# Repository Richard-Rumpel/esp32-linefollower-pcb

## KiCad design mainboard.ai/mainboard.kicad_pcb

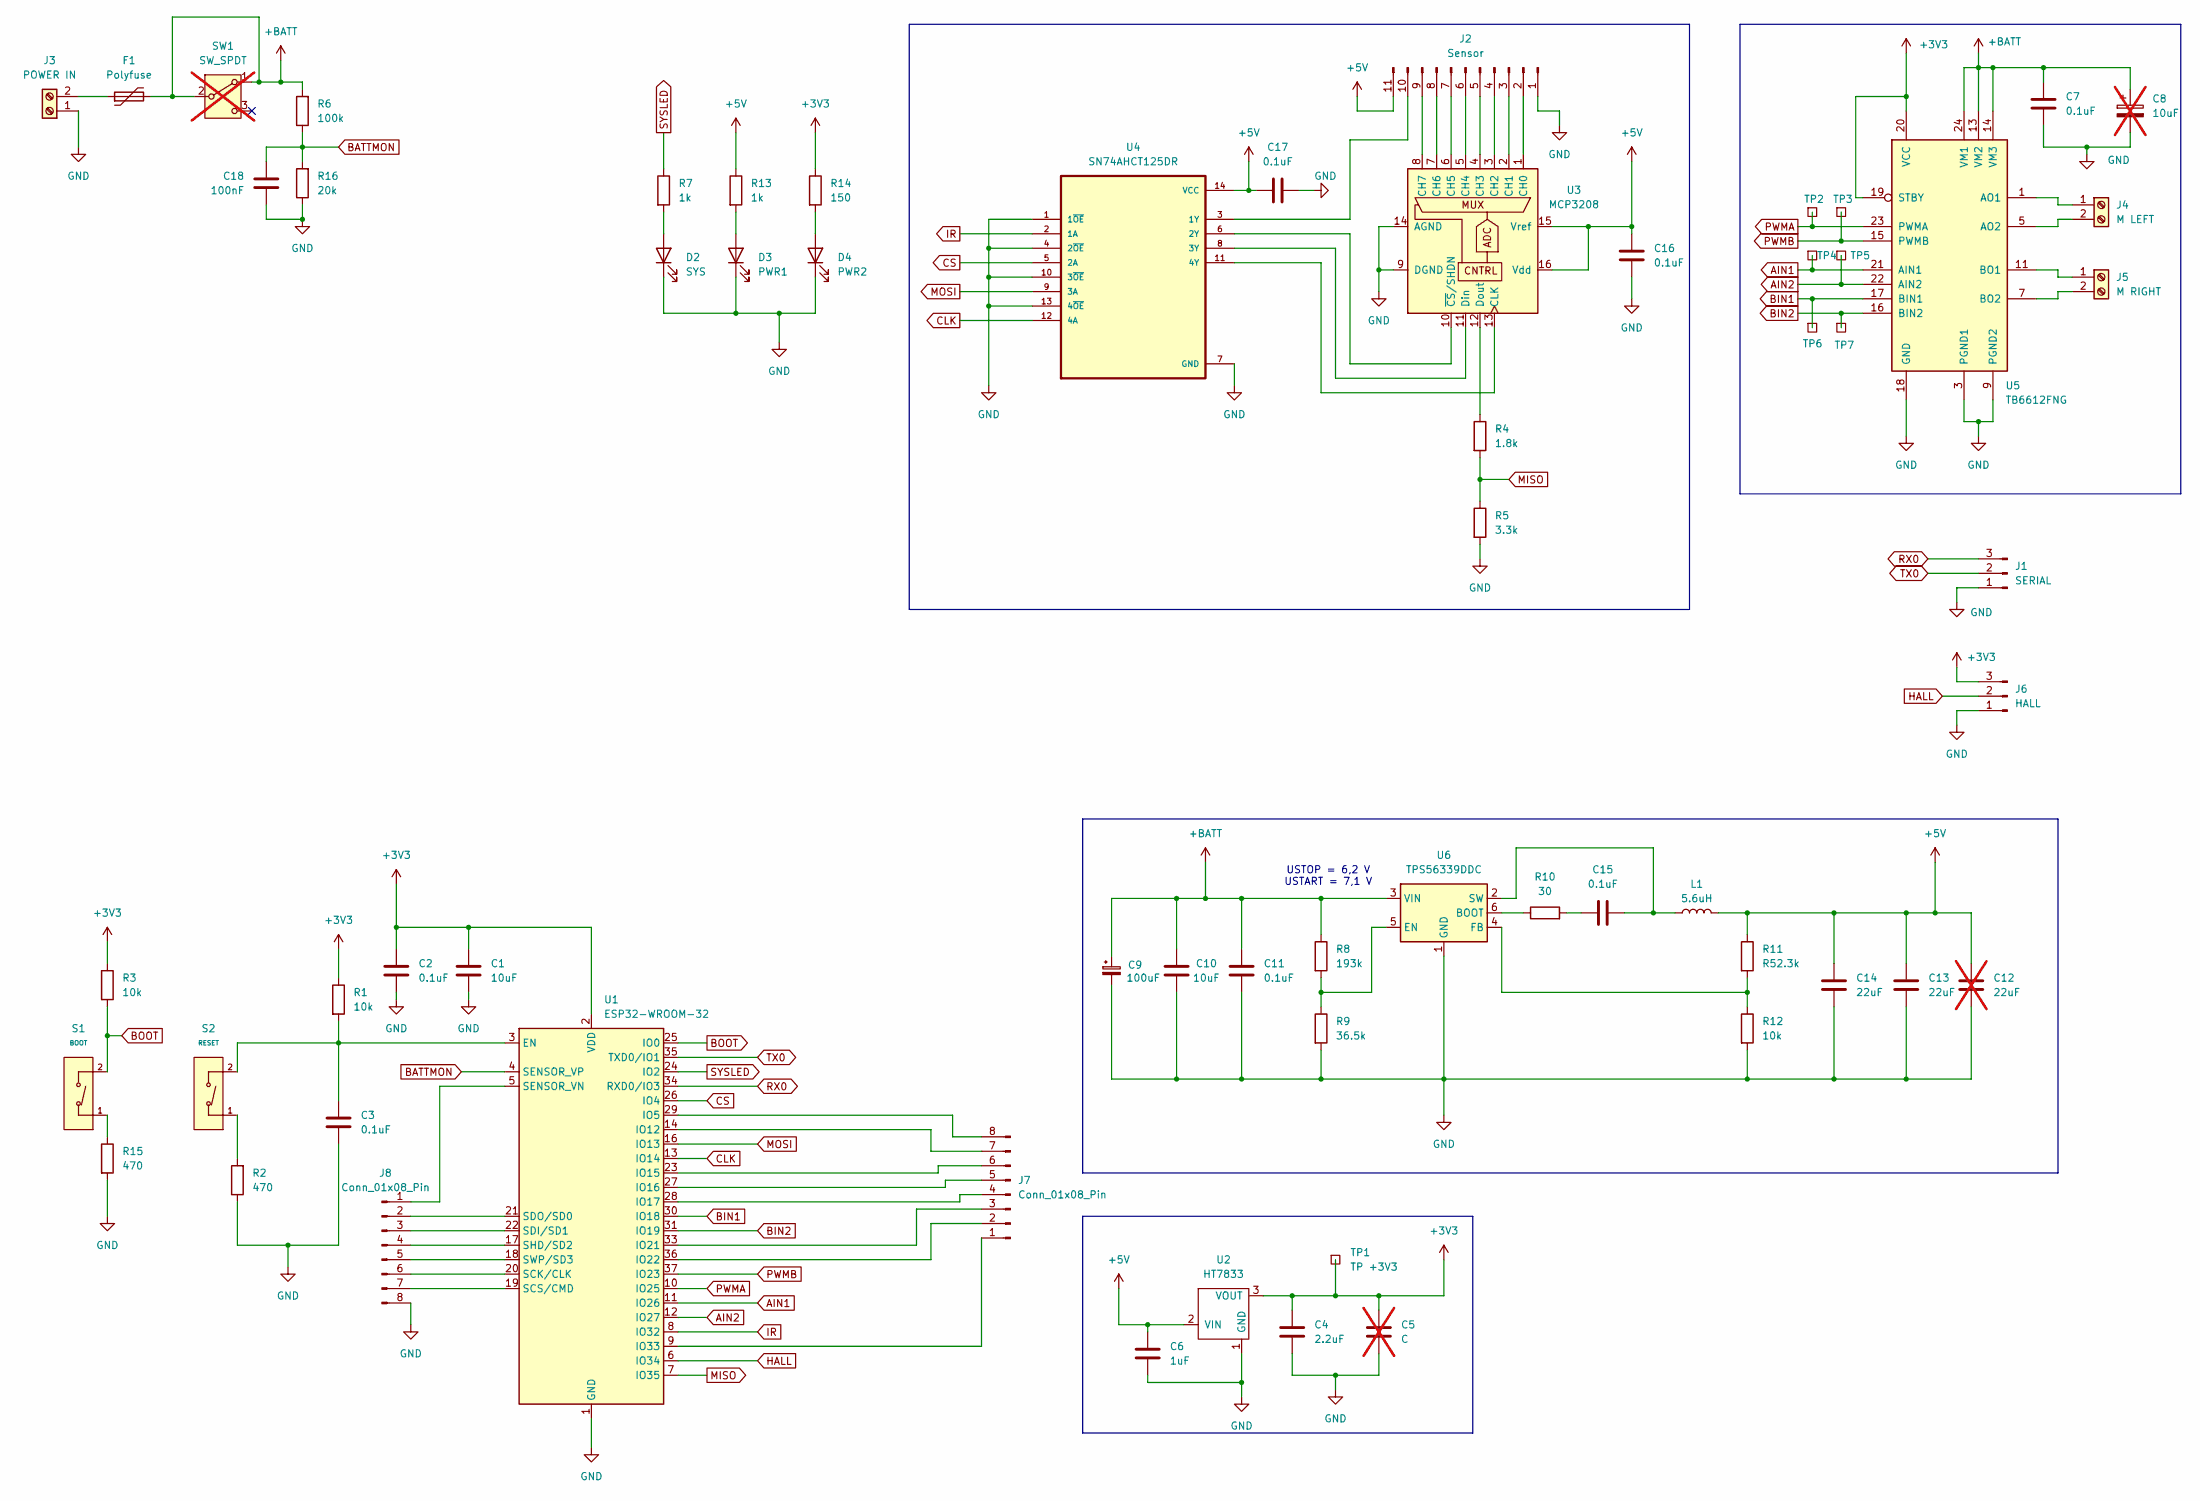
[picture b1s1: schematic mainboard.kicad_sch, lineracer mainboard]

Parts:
C1: 10uF; C_0603_1608Metric_Pad1.08x0.95mm_HandSolder; LCSC C1691
C2, C3: 0.1uF; C_0603_1608Metric_Pad1.08x0.95mm_HandSolder; LCSC C1590
C4: 2.2uF; C_0603_1608Metric_Pad1.08x0.95mm_HandSolder; LCSC C23630
C5: C; not fitted
C6: 1uF; C_0603_1608Metric_Pad1.08x0.95mm_HandSolder; LCSC C14664
C7: 0.1uF; C_0603_1608Metric_Pad1.08x0.95mm_HandSolder; LCSC C15850
C8: 10uF; not fitted
C9: 100uF; CP_Elec_6.3x7.7
C10: 10uF; C_0805_2012Metric_Pad1.18x1.45mm_HandSolder; LCSC C15850
C11, C16, C17: 0.1uF; C_0805_2012Metric_Pad1.18x1.45mm_HandSolder; LCSC C15850
C12: 22uF; not fitted
C13, C14: 22uF; C_0805_2012Metric_Pad1.18x1.45mm_HandSolder; LCSC C98190
C15: 0.1uF; C_0603_1608Metric_Pad1.08x0.95mm_HandSolder; LCSC C1591
C18: 100nF; C_0603_1608Metric_Pad1.08x0.95mm_HandSolder; LCSC C14663
D2: SYS; LED_0603_1608Metric_Pad1.05x0.95mm_HandSolder; LCSC C2286
D3: PWR1; LED_0603_1608Metric_Pad1.05x0.95mm_HandSolder; LCSC C2287
D4: PWR2; LED_0603_1608Metric_Pad1.05x0.95mm_HandSolder; LCSC C2288
F1: Polyfuse; Fuse_1812_4532Metric; LCSC C20812
J1: SERIAL; PinHeader_1x03_P2.54mm_Vertical
J2: Sensor; PinHeader_1x11_P2.54mm_Vertical
J3: POWER IN; TerminalBlock_Kangnex_WJ300V-5.0-2P_1x02_P5.00mm; LCSC C8385
J4: M LEFT; TerminalBlock_Kangnex_WJ300V-5.0-2P_1x02_P5.00mm; LCSC C8385
J5: M RIGHT; TerminalBlock_Kangnex_WJ300V-5.0-2P_1x02_P5.00mm; LCSC C8385
J6: HALL; PinHeader_1x03_P2.54mm_Vertical
J7, J8: Conn_01x08_Pin; PinHeader_1x08_P2.54mm_Vertical
L1: 5.6uH; L_0530CDMCCDS_5.4x5.2mm; LCSC C2961888
R1, R3: 10k; R_0603_1608Metric_Pad0.98x0.95mm_HandSolder; LCSC C25804
R2, R15: 470; R_0603_1608Metric_Pad0.98x0.95mm_HandSolder; LCSC C23179
R4: 1.8k; R_0603_1608Metric_Pad0.98x0.95mm_HandSolder; LCSC C4177
R5: 3.3k; R_0603_1608Metric_Pad0.98x0.95mm_HandSolder; LCSC C22978
R6: 100k; R_0603_1608Metric_Pad0.98x0.95mm_HandSolder; LCSC C25803
R7, R13: 1k; R_0603_1608Metric_Pad0.98x0.95mm_HandSolder; LCSC C21190
R8: 193k; R_0603_1608Metric_Pad0.98x0.95mm_HandSolder; LCSC C22932
R9: 36.5k; R_0603_1608Metric_Pad0.98x0.95mm_HandSolder; LCSC C23029
R10: 30; R_0603_1608Metric_Pad0.98x0.95mm_HandSolder; LCSC C22985
R11: R52.3k; R_0603_1608Metric_Pad0.98x0.95mm_HandSolder; LCSC C23198
R12: 10k; R_0603_1608Metric_Pad0.98x0.95mm_HandSolder; LCSC C98220
R14: 150; R_0603_1608Metric_Pad0.98x0.95mm_HandSolder; LCSC C22808
R16: 20k; R_0603_1608Metric_Pad0.98x0.95mm_HandSolder; LCSC C4184
S1: BOOT; SW_TS-1088-AR02016; Voltage Rating (Dc) 12V; Part TS-1088-AR02016; LCSC C720477
S2: RESET; SW_TS-1088-AR02016; Voltage Rating (Dc) 12V; Part TS-1088-AR02016; LCSC C720477
SW1: SW_SPDT; SW_SS-12D10L5; LCSC C319012; not fitted
TP1: TP +3V3; TestPoint_Pad_2.0x2.0mm
TP2, TP3, TP4, TP5, TP6, TP7: TestPoint_Square; TestPoint_Pad_2.0x2.0mm
U1: ESP32-WROOM-32; ESP32-WROOM-32E; LCSC C701341
U2: HT7833; SOT-89-3; LCSC C50936
U3: MCP3208; SOIC-16_L9.9-W3.9-P1.27-LS6.0-BL; LCSC C185809
U4: SN74AHCT125DR; SOIC-14_L8.7-W3.9-P1.27-LS6.0-BL; LCSC C155176
U5: TB6612FNG; SSOP-24_5.3x8.2mm_P0.65mm; LCSC C88224
U6: TPS56339DDC; SOT-23-6; LCSC C2071106

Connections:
+3V3: C1.1, C2.1, C4.1, C5.1, J6.3, R1.1, R3.1, R14.1, TP1.1, U1.2 (VDD), U2.3 (VOUT), U5.19 (STBY), U5.20 (VCC)
+5V: C6.1, C12.1, C13.1, C14.1, C16.1, C17.1, J2.11, L1.2, R11.1, R13.1, U2.2 (VIN), U3.15 (Vref), U3.16 (Vdd), U4.14 (VCC)
+BATT: C7.1, C8.1, C9.1, C10.1, C11.1, F1.2, R6.2, R8.1, SW1.1 (A), SW1.2 (B), U5.13 (VM2), U5.14 (VM3), U5.24 (VM1), U6.3 (VIN)
AIN1: TP4.1, U1.11 (IO26), U5.21 (AIN1)
AIN2: TP5.1, U1.12 (IO27), U5.22 (AIN2)
BATTMON: C18.1, R6.1, R16.2, U1.4 (SENSOR_VP)
BIN1: TP6.1, U1.30 (IO18), U5.17 (BIN1)
BIN2: TP7.1, U1.31 (IO19), U5.16 (BIN2)
BOOT: R3.2, S1.2 (B), U1.25 (IO0)
CLK: U1.13 (IO14), U4.12 (4A)
CS: U1.26 (IO4), U4.5 (2A)
GND: C1.2, C2.2, C3.2, C4.2, C5.2, C6.2, C7.2, C8.2, C9.2, C10.2, C11.2, C12.2, C13.2, C14.2, C16.2, C17.2, C18.2, D2.1 (K), D3.1 (K), D4.1 (K), J1.1, J2.1, J3.1, J6.1, J8.8, R2.1, R5.2, R9.2, R12.2, R15.2, R16.1, U1.1 (GND), U1.15 (GND), U1.38 (GND), U1.39 (GND), U2.1 (GND), U3.9 (DGND), U3.14 (AGND), U4.1 (1~OE), U4.4 (2~OE), U4.7 (GND), U4.10 (3~OE), U4.13 (4~OE), U5.3 (PGND1), U5.4 (PGND1), U5.9 (PGND2), U5.10 (PGND2), U5.18 (GND), U6.1 (GND)
HALL: J6.2, U1.6 (IO34)
IR: U1.8 (IO32), U4.2 (1A)
MISO: R4.2, R5.1, U1.7 (IO35)
MOSI: U1.16 (IO13), U4.9 (3A)
unnamed: C15.1, R10.2
unnamed: D2.2 (A), R7.2
unnamed: D3.2 (A), R13.2
unnamed: D4.2 (A), R14.2
unnamed: J2.2, U3.1 (CH0)
unnamed: J2.3, U3.2 (CH1)
unnamed: J2.4, U3.3 (CH2)
unnamed: J2.5, U3.4 (CH3)
unnamed: J2.6, U3.5 (CH4)
unnamed: J2.7, U3.6 (CH5)
unnamed: J2.8, U3.7 (CH6)
unnamed: J2.9, U3.8 (CH7)
unnamed: J2.10, U4.3 (1Y)
unnamed: F1.1, J3.2
unnamed: J4.1, U5.1 (AO1), U5.2 (AO1)
unnamed: J4.2, U5.5 (AO2), U5.6 (AO2)
unnamed: J5.1, U5.11 (BO1), U5.12 (BO1)
unnamed: J5.2, U5.7 (BO2), U5.8 (BO2)
unnamed: J7.1, U1.9 (IO33)
unnamed: J7.2, U1.36 (IO22)
unnamed: J7.3, U1.33 (IO21)
unnamed: J7.4, U1.28 (IO17)
unnamed: J7.5, U1.27 (IO16)
unnamed: J7.6, U1.23 (IO15)
unnamed: J7.7, U1.14 (IO12)
unnamed: J7.8, U1.29 (IO5)
unnamed: J8.1, U1.5 (SENSOR_VN)
unnamed: J8.2, U1.21 (SDO/SD0)
unnamed: J8.3, U1.22 (SDI/SD1)
unnamed: J8.4, U1.17 (SHD/SD2)
unnamed: J8.5, U1.18 (SWP/SD3)
unnamed: J8.6, U1.20 (SCK/CLK)
unnamed: J8.7, U1.19 (SCS/CMD)
unnamed: R15.1, S1.1 (A)
unnamed: R2.2, S2.1 (A)
unnamed: C3.1, R1.2, S2.2 (B), U1.3 (EN)
unnamed: U3.13 (CLK), U4.11 (4Y)
unnamed: U3.11 (Din), U4.8 (3Y)
unnamed: R4.1, U3.12 (Dout)
unnamed: U3.10 (~CS/SHDN), U4.6 (2Y)
unnamed: R10.1, U6.6 (BOOT)
unnamed: R8.2, R9.1, U6.5 (EN)
unnamed: R11.2, R12.1, U6.4 (FB)
unnamed: C15.2, L1.1, U6.2 (SW)
PWMA: TP2.1, U1.10 (IO25), U5.23 (PWMA)
PWMB: TP3.1, U1.37 (IO23), U5.15 (PWMB)
RX0: J1.3, U1.34 (RXD0/IO3)
SYSLED: R7.1, U1.24 (IO2)
TX0: J1.2, U1.35 (TXD0/IO1)

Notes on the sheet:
USTOP = 6,2 V USTART = 7,1 V

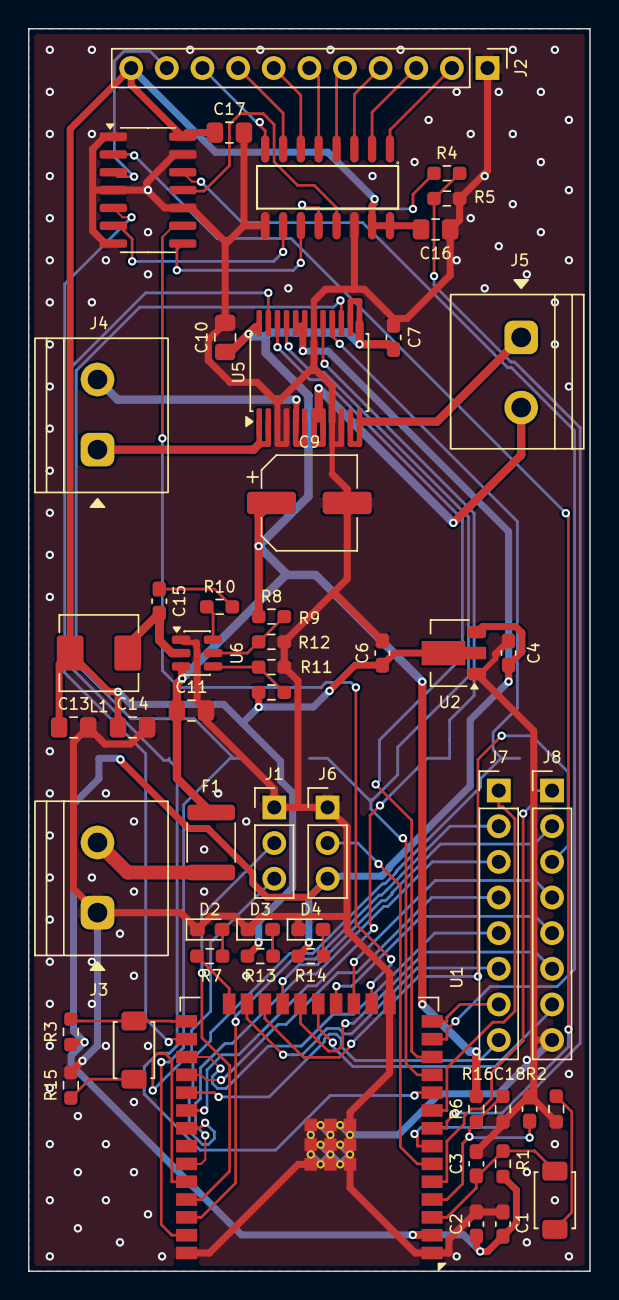
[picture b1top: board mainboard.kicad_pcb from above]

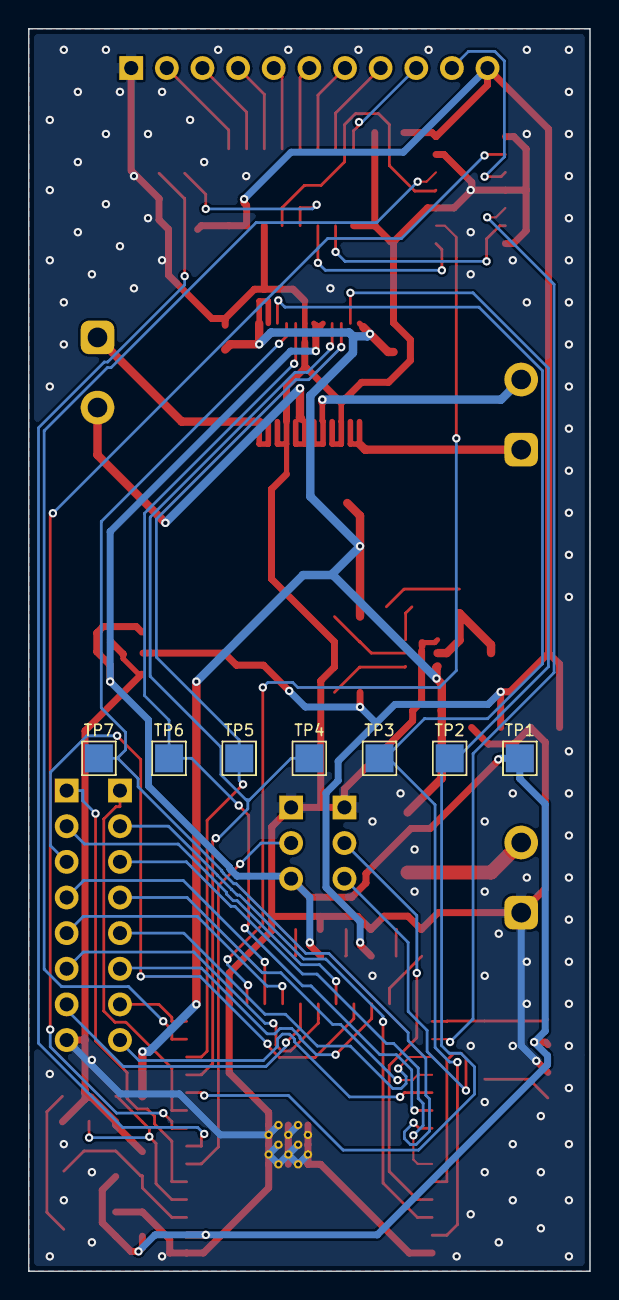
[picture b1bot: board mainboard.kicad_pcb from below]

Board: 2 copper layers, 40.0 x 88.6 mm, 59 parts (7 on the bottom side), 65 nets.

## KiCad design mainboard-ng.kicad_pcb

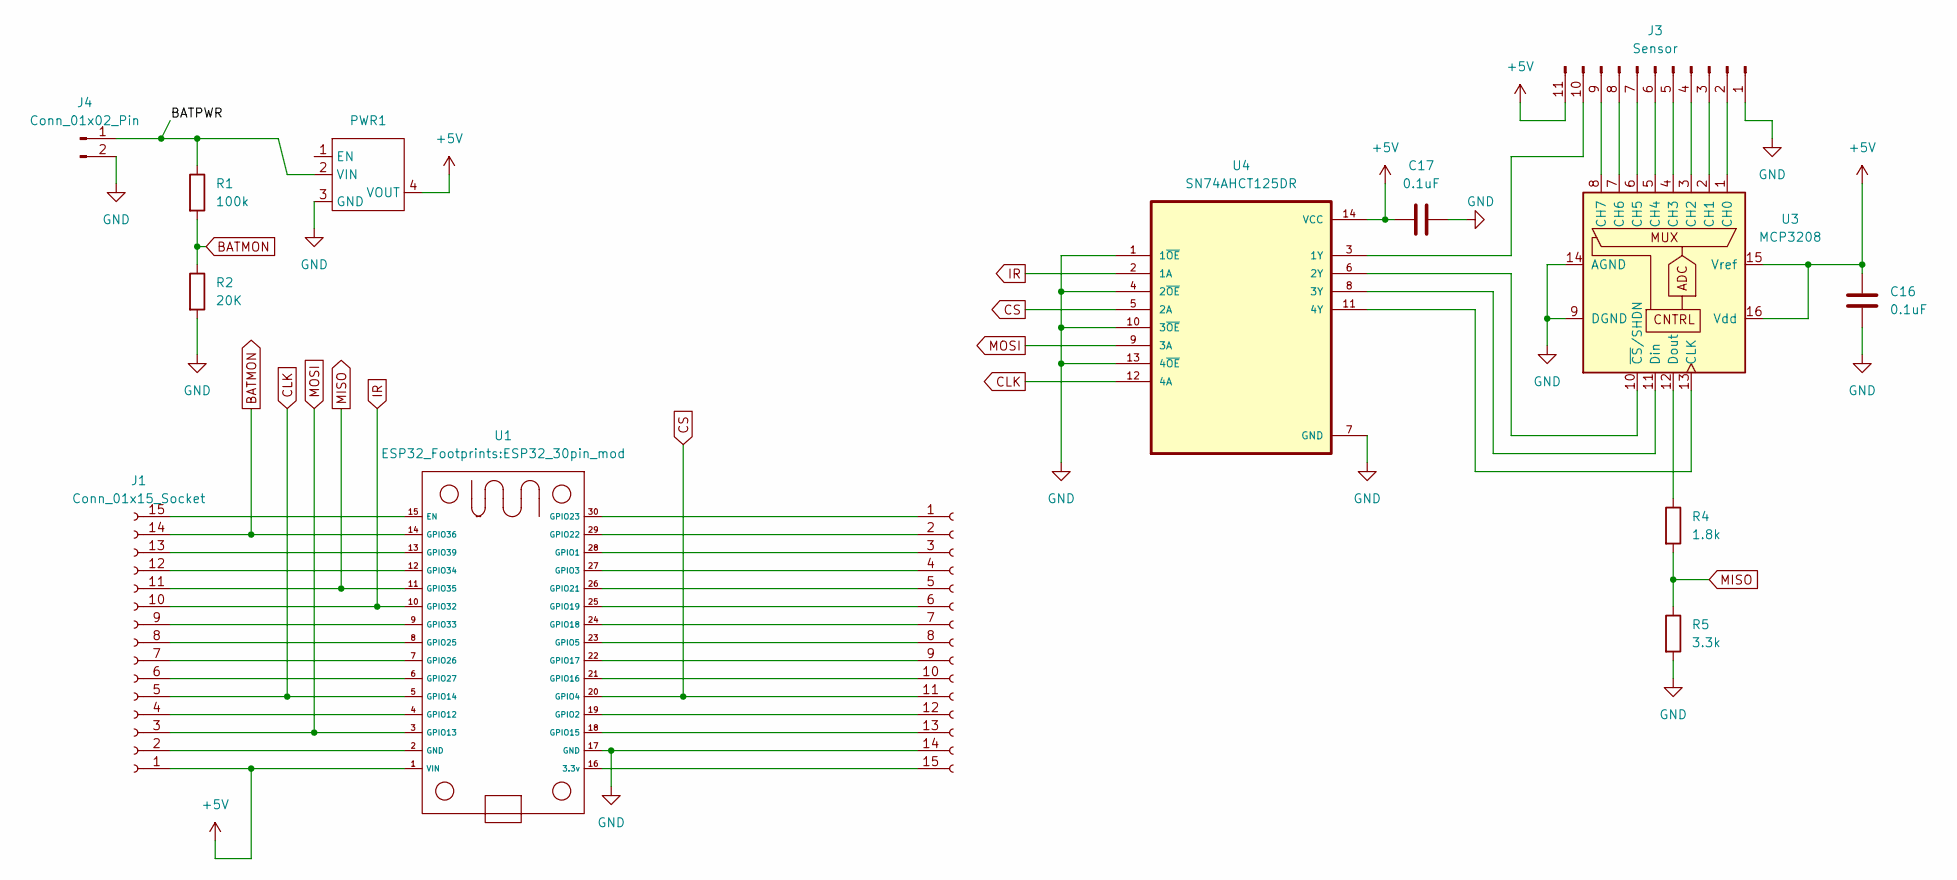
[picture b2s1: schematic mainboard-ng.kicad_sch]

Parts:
C16, C17: 0.1uF; C_0805_2012Metric_Pad1.18x1.45mm_HandSolder
J1, J2: Conn_01x15_Socket; PinSocket_1x15_P2.54mm_Vertical
J3: Sensor; PinHeader_1x11_P2.54mm_Vertical
J4: Conn_01x02_Pin; PinSocket_1x02_P2.54mm_Vertical
PWR1: PWR
R1: 100k; R_Axial_DIN0309_L9.0mm_D3.2mm_P5.08mm_Vertical
R2: 20K; R_Axial_DIN0309_L9.0mm_D3.2mm_P5.08mm_Vertical
R4: 1.8k; R_Axial_DIN0309_L9.0mm_D3.2mm_P5.08mm_Vertical
R5: 3.3k; R_Axial_DIN0309_L9.0mm_D3.2mm_P5.08mm_Vertical; LCSC C22978
U1: ESP32_30pin_mod
U3: MCP3208; DIP-16_W7.62mm_LongPads; LCSC C185809
U4: SN74AHCT125DR; DIP-14_W10.16mm_LongPads

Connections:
+5V: C16.1, C17.1, J1.1, J3.11, PWR1.4 (VOUT), U1.1 (VIN), U3.15 (Vref), U3.16 (Vdd), U4.14 (VCC)
/BATPWR: J4.1, PWR1.2 (VIN), R1.1
BATMON: J1.14, R1.2, R2.1, U1.14 (GPIO36)
CLK: J1.5, U1.5 (GPIO14), U4.12 (4A)
CS: J2.11, U1.20 (GPIO4), U4.5 (2A)
GND: C16.2, C17.2, J2.14, J3.1, J4.2, PWR1.3 (GND), R2.2, R5.2, U1.17 (GND), U3.9 (DGND), U3.14 (AGND), U4.1 (1~OE), U4.4 (2~OE), U4.7 (GND), U4.10 (3~OE), U4.13 (4~OE)
IR: J1.10, U1.10 (GPIO32), U4.2 (1A)
MISO: J1.11, R4.2, R5.1, U1.11 (GPIO35)
MOSI: J1.3, U1.3 (GPIO13), U4.9 (3A)
unnamed: J1.2, U1.2 (GND)
unnamed: J1.4, U1.4 (GPIO12)
unnamed: J1.6, U1.6 (GPIO27)
unnamed: J1.7, U1.7 (GPIO26)
unnamed: J1.8, U1.8 (GPIO25)
unnamed: J1.9, U1.9 (GPIO33)
unnamed: J1.12, U1.12 (GPIO34)
unnamed: J1.13, U1.13 (GPIO39)
unnamed: J1.15, U1.15 (EN)
unnamed: J2.1, U1.30 (GPIO23)
unnamed: J2.2, U1.29 (GPIO22)
unnamed: J2.3, U1.28 (GPIO1)
unnamed: J2.4, U1.27 (GPIO3)
unnamed: J2.5, U1.26 (GPIO21)
unnamed: J2.6, U1.25 (GPIO19)
unnamed: J2.7, U1.24 (GPIO18)
unnamed: J2.8, U1.23 (GPIO5)
unnamed: J2.9, U1.22 (GPIO17)
unnamed: J2.10, U1.21 (GPIO16)
unnamed: J2.12, U1.19 (GPIO2)
unnamed: J2.13, U1.18 (GPIO15)
unnamed: J2.15, U1.16 (3.3v)
unnamed: J3.2, U3.1 (CH0)
unnamed: J3.3, U3.2 (CH1)
unnamed: J3.4, U3.3 (CH2)
unnamed: J3.5, U3.4 (CH3)
unnamed: J3.6, U3.5 (CH4)
unnamed: J3.7, U3.6 (CH5)
unnamed: J3.8, U3.7 (CH6)
unnamed: J3.9, U3.8 (CH7)
unnamed: J3.10, U4.3 (1Y)
unnamed: U3.13 (CLK), U4.11 (4Y)
unnamed: U3.11 (Din), U4.8 (3Y)
unnamed: R4.1, U3.12 (Dout)
unnamed: U3.10 (~CS/SHDN), U4.6 (2Y)

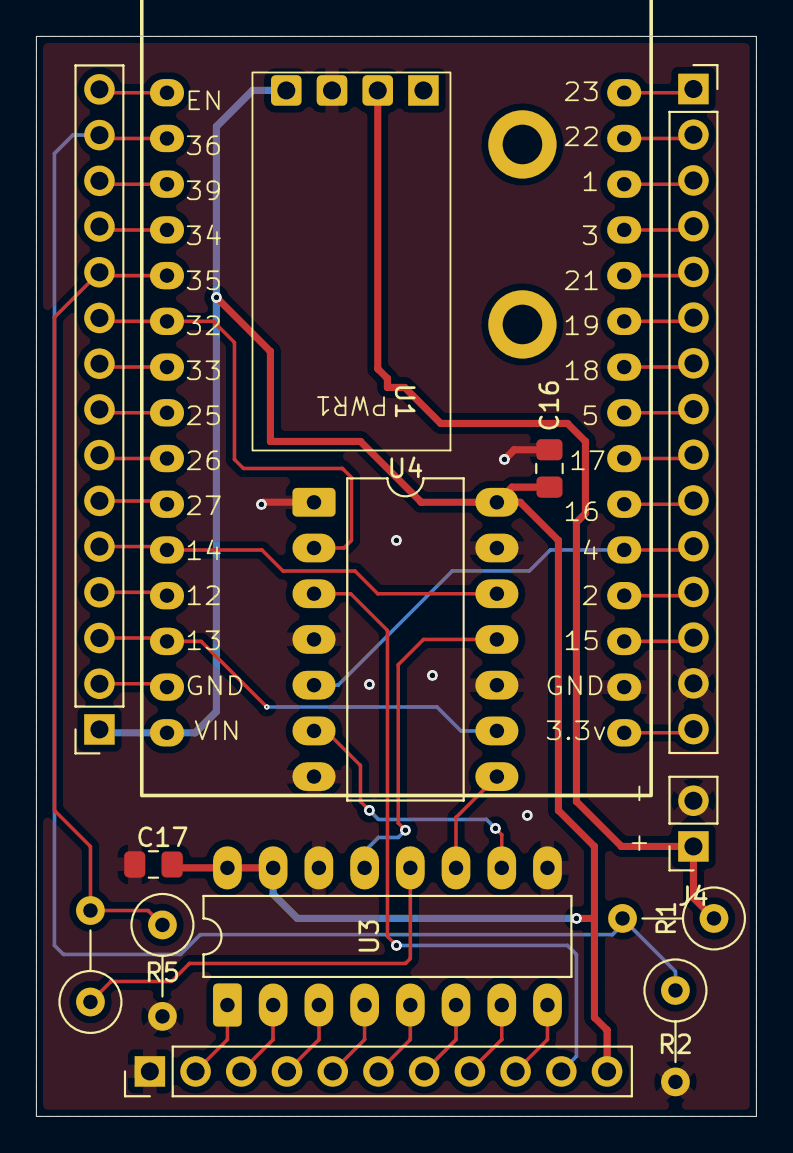
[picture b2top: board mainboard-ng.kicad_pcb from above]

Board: 2 copper layers, 40.0 x 60.0 mm, 14 parts (0 on the bottom side), 44 nets.
